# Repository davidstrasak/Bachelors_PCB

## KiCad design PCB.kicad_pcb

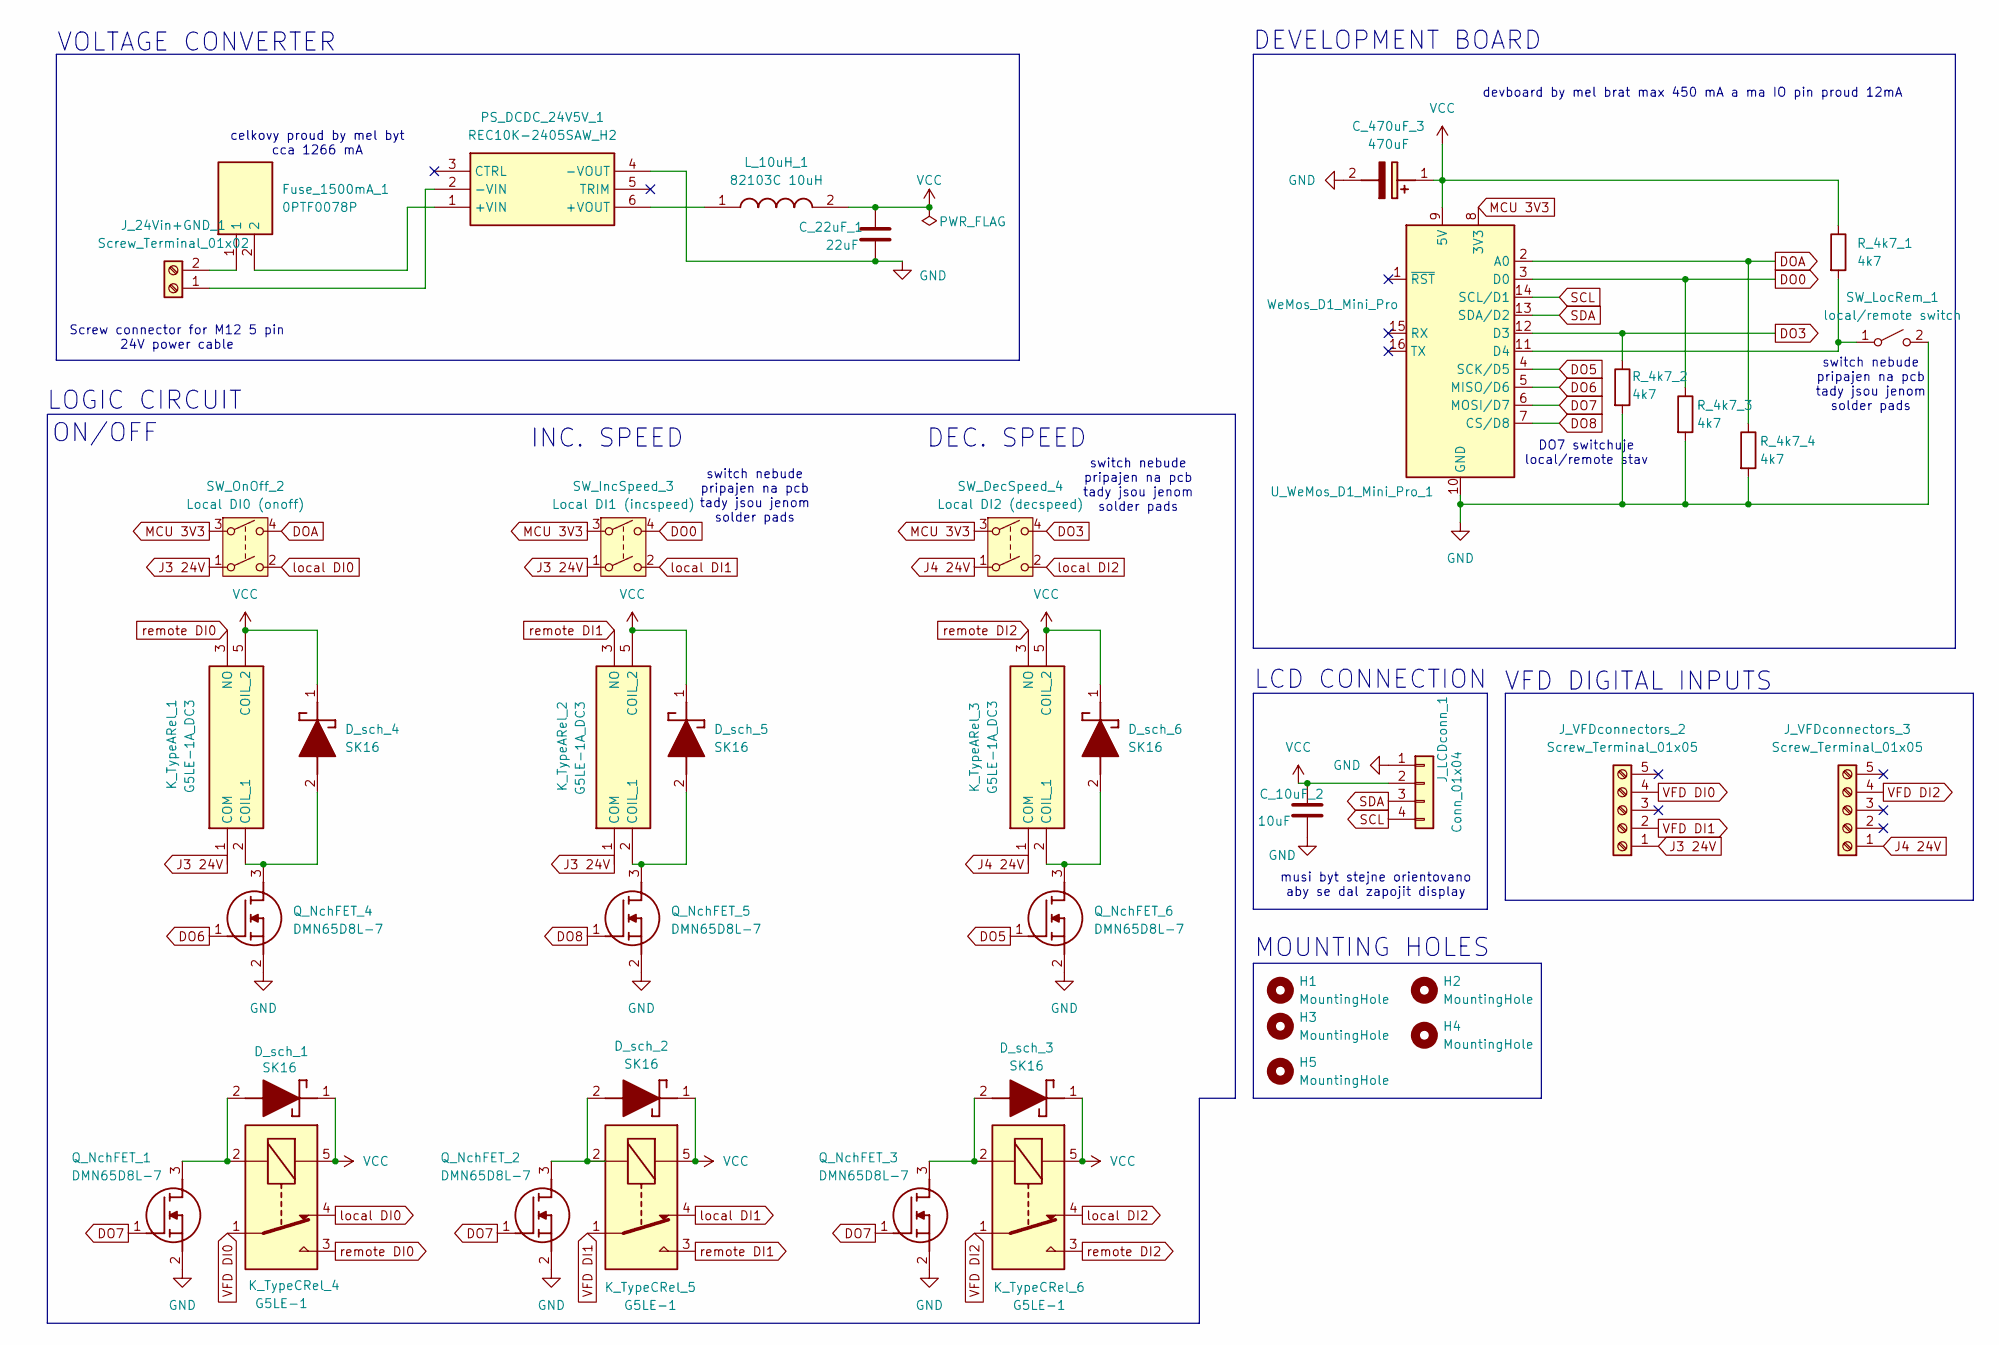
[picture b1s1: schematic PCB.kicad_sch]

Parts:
C_10uF_2: 10uF; C_0603_1608Metric
C_22uF_1: 22uF; C_0603_1608Metric
C_470uF_3: 470uF; CAPPRD250W52D630H1250; Mouser Part Number 710-860010273011
D_sch_1, D_sch_2, D_sch_3, D_sch_4, D_sch_5, D_sch_6: SK16; DIOM5027X250N; Mouser Part Number 637-SK16
Fuse_1500mA_1: 0PTF0078P; Mouser Part Number 576-0PTF0078P
H1: MountingHole; MountingHole_5mm
H2, H3, H5: MountingHole; MountingHole_3mm
H4: MountingHole; MountingHole_4mm
J_24Vin+GND_1: Screw_Terminal_01x02; 1729128
J_LCDconn_1: Conn_01x04; PinHeader_1x04_P2.54mm_Horizontal
J_VFDconnectors_2, J_VFDconnectors_3: Screw_Terminal_01x05; 1935190
K_TypeARel_1, K_TypeARel_2, K_TypeARel_3: G5LE-1A_DC3; G5LE1A4DC5; Mouser Part Number 653-G5LE-1ADC3
K_TypeCRel_4, K_TypeCRel_5, K_TypeCRel_6: G5LE-1; G5LE1DC3
L_10uH_1: 82103C 10uH; 8200; Mouser Part Number 580-82103C
PS_DCDC_24V5V_1: REC10K-2405SAW_H2; REC10K-AW; Manufacturer_Part_Number REC10K-2405SAW/H2
Q_NchFET_1, Q_NchFET_2, Q_NchFET_3, Q_NchFET_4, Q_NchFET_5, Q_NchFET_6: DMN65D8L-7; SOT96P240X115-3N; Mouser Part Number 621-DMN65D8L-7
R_4k7_1, R_4k7_2, R_4k7_3, R_4k7_4: 4k7; R_0603_1608Metric
SW_DecSpeed_4: Local DI2 (decspeed); 1935187
SW_IncSpeed_3: Local DI1 (incspeed); 1935187
SW_LocRem_1: local/remote switch; 1729128
SW_OnOff_2: Local DI0 (onoff); 1935187
U_WeMos_D1_Mini_Pro_1: WeMos_D1_Mini_Pro; WEMOS_D1_mini_light

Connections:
DO0: R_4k7_3.1, SW_IncSpeed_3.4, U_WeMos_D1_Mini_Pro_1.3 (D0)
DO3: R_4k7_2.1, SW_DecSpeed_4.4, U_WeMos_D1_Mini_Pro_1.12 (D3)
DO5: Q_NchFET_6.1 (G), U_WeMos_D1_Mini_Pro_1.4 (SCK/D5)
DO6: Q_NchFET_4.1 (G), U_WeMos_D1_Mini_Pro_1.5 (MISO/D6)
DO7: Q_NchFET_1.1 (G), Q_NchFET_2.1 (G), Q_NchFET_3.1 (G), U_WeMos_D1_Mini_Pro_1.6 (MOSI/D7)
DO8: Q_NchFET_5.1 (G), U_WeMos_D1_Mini_Pro_1.7 (CS/D8)
DOA: R_4k7_4.1, SW_OnOff_2.4, U_WeMos_D1_Mini_Pro_1.2 (A0)
GND: C_10uF_2.2, C_22uF_1.2, C_470uF_3.2 (-), J_LCDconn_1.1, PS_DCDC_24V5V_1.4 (-VOUT), Q_NchFET_1.2 (S), Q_NchFET_2.2 (S), Q_NchFET_3.2 (S), Q_NchFET_4.2 (S), Q_NchFET_5.2 (S), Q_NchFET_6.2 (S), R_4k7_2.2, R_4k7_3.2, R_4k7_4.2, SW_LocRem_1.2 (B), U_WeMos_D1_Mini_Pro_1.10 (GND)
J3 24V: J_VFDconnectors_2.1, K_TypeARel_1.1 (COM), K_TypeARel_2.1 (COM), SW_IncSpeed_3.1, SW_OnOff_2.1
J4 24V: J_VFDconnectors_3.1, K_TypeARel_3.1 (COM), SW_DecSpeed_4.1
MCU 3V3: SW_DecSpeed_4.3, SW_IncSpeed_3.3, SW_OnOff_2.3, U_WeMos_D1_Mini_Pro_1.8 (3V3)
unnamed: D_sch_1.2 (A), K_TypeCRel_4.2, Q_NchFET_1.3 (D)
unnamed: D_sch_2.2 (A), K_TypeCRel_5.2, Q_NchFET_2.3 (D)
unnamed: D_sch_3.2 (A), K_TypeCRel_6.2, Q_NchFET_3.3 (D)
unnamed: D_sch_4.2 (A), K_TypeARel_1.2 (COIL_1), Q_NchFET_4.3 (D)
unnamed: D_sch_5.2 (A), K_TypeARel_2.2 (COIL_1), Q_NchFET_5.3 (D)
unnamed: D_sch_6.2 (A), K_TypeARel_3.2 (COIL_1), Q_NchFET_6.3 (D)
unnamed: J_24Vin+GND_1.1, PS_DCDC_24V5V_1.2 (-VIN)
unnamed: Fuse_1500mA_1.1, J_24Vin+GND_1.2
unnamed: Fuse_1500mA_1.2, PS_DCDC_24V5V_1.1 (+VIN)
unnamed: L_10uH_1.1, PS_DCDC_24V5V_1.6 (+VOUT)
unnamed: R_4k7_1.2, SW_LocRem_1.1 (A), U_WeMos_D1_Mini_Pro_1.11 (D4)
SCL: J_LCDconn_1.4, U_WeMos_D1_Mini_Pro_1.14 (SCL/D1)
SDA: J_LCDconn_1.3, U_WeMos_D1_Mini_Pro_1.13 (SDA/D2)
VCC: C_10uF_2.1, C_22uF_1.1, C_470uF_3.1 (+), D_sch_1.1 (K), D_sch_2.1 (K), D_sch_3.1 (K), D_sch_4.1 (K), D_sch_5.1 (K), D_sch_6.1 (K), J_LCDconn_1.2, K_TypeARel_1.5 (COIL_2), K_TypeARel_2.5 (COIL_2), K_TypeARel_3.5 (COIL_2), K_TypeCRel_4.5, K_TypeCRel_5.5, K_TypeCRel_6.5, L_10uH_1.2, R_4k7_1.1, U_WeMos_D1_Mini_Pro_1.9 (5V)
VFD DI0: J_VFDconnectors_2.4, K_TypeCRel_4.1
VFD DI1: J_VFDconnectors_2.2, K_TypeCRel_5.1
VFD DI2: J_VFDconnectors_3.4, K_TypeCRel_6.1
local DI0: K_TypeCRel_4.4, SW_OnOff_2.2
local DI1: K_TypeCRel_5.4, SW_IncSpeed_3.2
local DI2: K_TypeCRel_6.4, SW_DecSpeed_4.2
remote DI0: K_TypeARel_1.3 (NO), K_TypeCRel_4.3
remote DI1: K_TypeARel_2.3 (NO), K_TypeCRel_5.3
remote DI2: K_TypeARel_3.3 (NO), K_TypeCRel_6.3

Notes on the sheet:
DEVELOPMENT BOARD
LOGIC CIRCUIT
DO7 switchuje local/remote stav
MOUNTING HOLES
musi byt stejne orientovano aby se dal zapojit display
VFD DIGITAL INPUTS
DEC. SPEED
VOLTAGE CONVERTER
celkovy proud by mel byt cca 1266 mA
switch nebude pripajen na pcb tady jsou jenom solder pads
devboard by mel brat max 450 mA a ma IO pin proud 12mA
ON/OFF
LCD CONNECTION
Screw connector for M12 5 pin 24V power cable
INC. SPEED

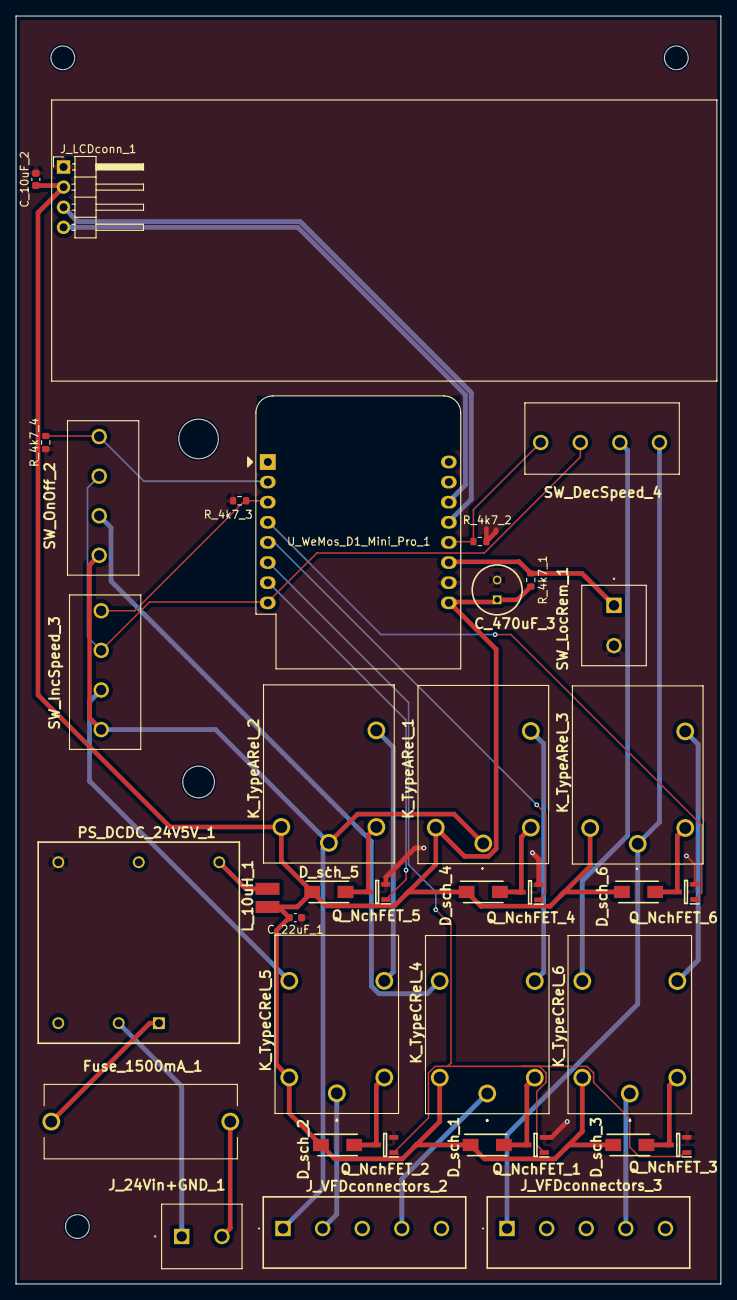
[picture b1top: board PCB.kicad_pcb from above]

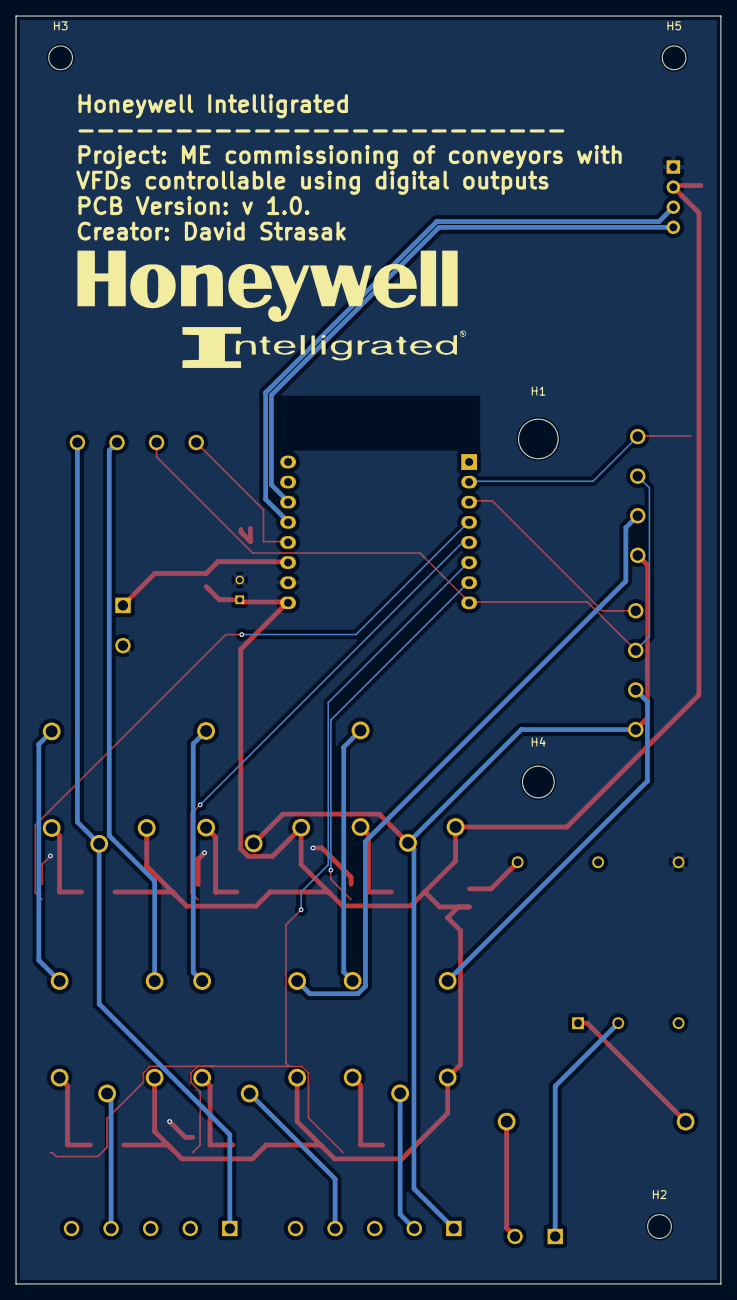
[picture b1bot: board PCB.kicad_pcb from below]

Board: 2 copper layers, 89.0 x 160.1 mm, 42 parts (5 on the bottom side), 34 nets.

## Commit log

2024-11-03 remove the lots of vias so the layout is cleaner
2024-11-04 update the pcb silkscreen names and start widening paths
2024-11-05 widen tracks with larger current and fix the local/remote switch footprint
2024-11-15 start improving the pcb schematic as per feedback no 2
2024-11-16 oprava schematu: zvoleni spravneho menice, pridani MOSFETu i k horni rade relay, move pojistky pred menicem a zvetseni hodnoty aby to utahla
2024-11-17 aktualizace pcb na zaklade predeslych oprav
2024-11-17 aktualizace par jmen ve schematu a prave jdu na updatovani pcb
2024-11-17 prvni aktualizace jmen done
2024-11-17 change the names of the schematic
2024-11-17 update the pcb
2024-11-17 zmena nazvu v schemu logickym obvodu
2024-11-17 finalni uprava nazvu na pcb
2024-11-17 uprava textu na pcb aby byl videt i pod komponenty
2024-11-25 Vymena der s reliefem za screw-in connectory
2024-11-25 komponenty jsou rozlozeny spravne a zacinam delat cesty
2024-11-25 zacal jsem wirovat draty a via
2024-11-25 dodelani wiringu pro desku v3 co ma vsechny komponenty nahore
2024-11-25 rewire dratu at je to nyni lepsi
2024-11-25 deska je erc-error free
2024-11-25 generovany gerbery z projektu
2024-11-26 vytvoreni a pridani linku do BOM
